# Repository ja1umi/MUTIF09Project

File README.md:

# MUTIF09 Project

MUTIF09 (or shortly MUTIF) project is my hobby project for developent of tiny homebrew computers and their add-on/expansion boards (e.g. Arithmetic coprocessor and I/O expansion board) simple enough for building and maintenance, focusing on around 1980s-era microprocessors (e.g. Motorola's MC6809, Harris' HD-6120) just for fun.

FAQ

1. When are updates available?

    Updates are available when they are released.

2. What does MUTIF mean?

    MUTIF is an anagram of two amaterur radio call signs of my own (suffix only).

3. How to assemble these things? / Where is the assembly manual?

    Refer to the schematic(s), order the PCB(s), collect parts required, populate the parts on the PCB just as you did in your other DIY electronics project. Knowledge of basic soldering techniques is also required. Remember to get your PC ready for USB-TTL serial cable installed.

    Like other open source projects, documents, sample programs and ohter design materials contained in this repository are provided *"as is"* without warranty.

    As for assembly manual(s), you can download the document(s) (e.g. *"Technical memorandum on MUTIF09 6809 Single Board Computer"* ) (for a fee) from BOOTH online store. Note: these booklet(s) are written in Japanese only.

    https://m-nihombashi.booth.pm/
    
    Or, you can get a copy at *doujinshi* sales exhibitions (e.g. Comic Maket, TechBookFest, Micom-Infinite PRO-68K).
    
    **I encourage you to get your copy of the booklet (if necessary) at the online store ( https://m-nihombashi.booth.pm/ ) due to the COVID-19 situation.**

4. Where is the document(s) about xxx?
    
    I know that documentation is insufficient, however, document preparation is still underway...

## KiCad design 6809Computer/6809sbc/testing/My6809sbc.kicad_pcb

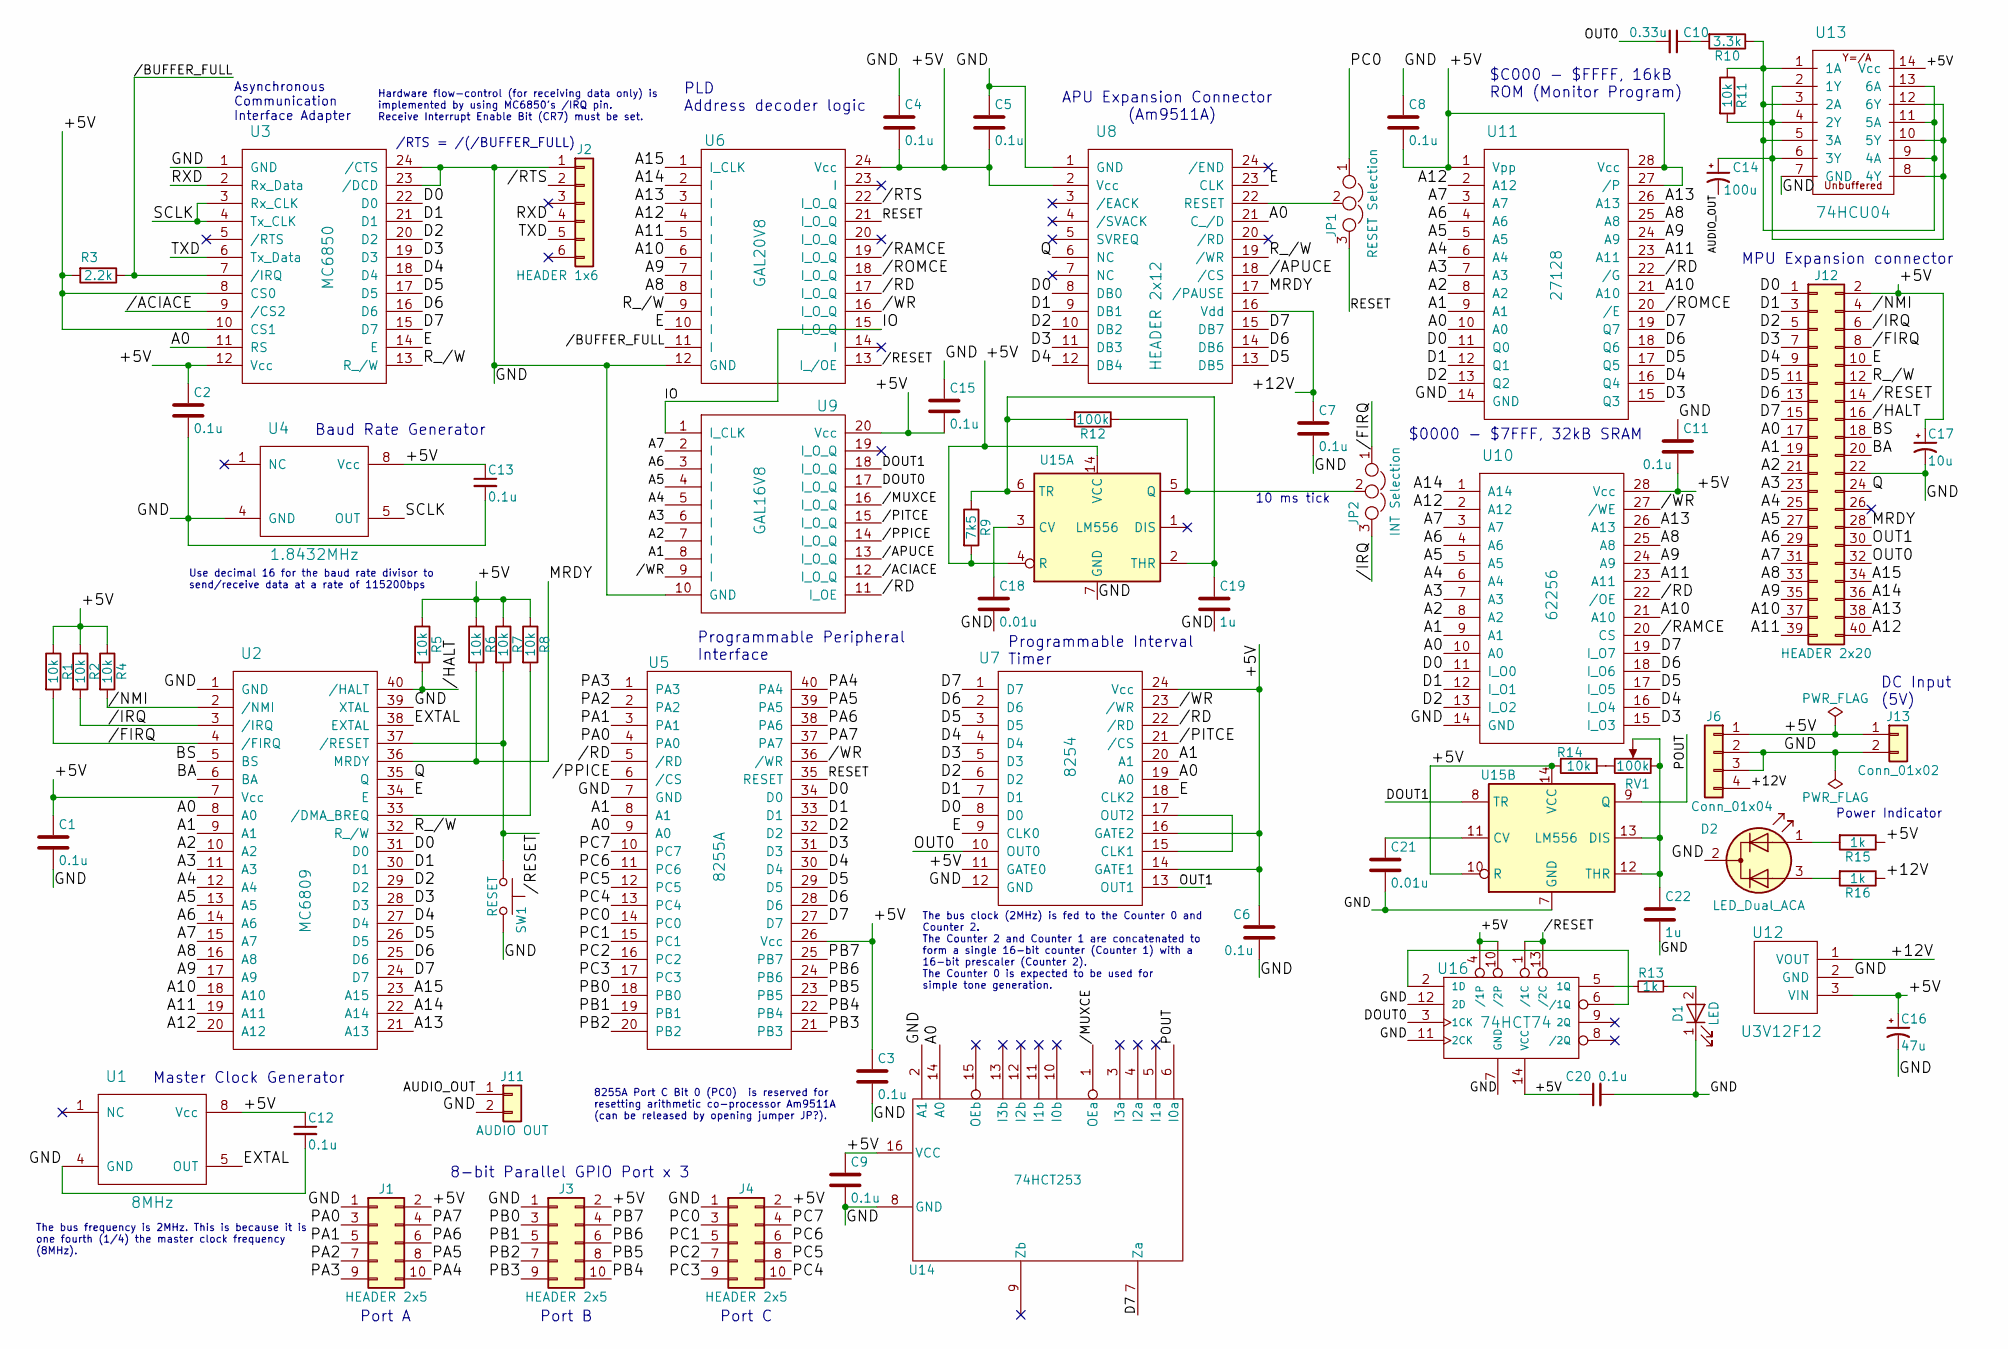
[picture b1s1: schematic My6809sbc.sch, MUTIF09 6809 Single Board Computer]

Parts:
C1, C2, C3, C4, C5, C6, C7, C8, C9, C11, C12, C13, C15, C20: 0.1u; C_Disc_D5.0mm_W2.5mm_P5.00mm
C10: 0.33u; C_Rect_L7.2mm_W3.5mm_P5.00mm_FKS2_FKP2_MKS2_MKP2
C14: 100u; CP_Radial_D8.0mm_P2.50mm
C16: 47u; CP_Radial_D5.0mm_P2.50mm
C17: 10u; CP_Radial_D5.0mm_P2.50mm
C18, C21: 0.01u; C_Disc_D5.0mm_W2.5mm_P5.00mm
C19, C22: 1u; C_Disc_D5.0mm_W2.5mm_P5.00mm
D1: LED; LED_D5.0mm
D2: LED_Dual_ACA; LED_D5.0mm-3
J1, J3, J4: HEADER 2x5; Pin_Header_Angled_2x05_Pitch2.54mm
J2: HEADER 1x6; Pin_Header_Angled_1x06_Pitch2.54mm
J6: Conn_01x04; Pin_Header_Straight_1x04_Pitch2.54mm
J11: AUDIO OUT; Pin_Header_Straight_1x02_Pitch2.54mm
J12: HEADER 2x20; Pin_Header_Straight_2x20_Pitch2.54mm
J13: Conn_01x02; Pin_Header_Straight_1x02_Pitch2.54mm
JP1: RESET Selection; Pin_Header_Straight_1x03_Pitch2.54mm
JP2: INT Selection; Pin_Header_Straight_1x03_Pitch2.54mm
R1, R2, R4, R5, R6, R7, R8, R11, R14: 10k; R_Axial_DIN0207_L6.3mm_D2.5mm_P10.16mm_Horizontal
R3: 2.2k; R_Axial_DIN0207_L6.3mm_D2.5mm_P10.16mm_Horizontal
R9: 7k5; R_Axial_DIN0207_L6.3mm_D2.5mm_P10.16mm_Horizontal
R10: 3.3k; R_Axial_DIN0207_L6.3mm_D2.5mm_P10.16mm_Horizontal
R12: 100k; R_Axial_DIN0207_L6.3mm_D2.5mm_P10.16mm_Horizontal
R13, R15, R16: 1k; R_Axial_DIN0207_L6.3mm_D2.5mm_P10.16mm_Horizontal
RV1: 100k; Potentiometer_WirePads_Small
SW1: RESET; SW_Tactile_Straight_KSA0Axx1LFTR
U1: 8MHz; Oscillator_DIP-8
U2: MC6809; DIP-40_W15.24mm_Socket
U3: MC6850; DIP-24_W15.24mm_Socket
U4: 1.8432MHz; Oscillator_DIP-8
U5: 8255A; DIP-40_W15.24mm_Socket
U6: GAL20V8; DIP-24_W7.62mm_Socket
U7: 8254; DIP-24_W15.24mm_Socket
U8: HEADER 2x12; DIP-24_W15.24mm_Socket
U9: GAL16V8; DIP-20_W7.62mm_Socket
U10: 62256; DIP-28_W15.24mm_Socket
U11: 27128; DIP-28_W15.24mm_Socket
U12: U3V12F12; Pin_Header_Straight_1x03_Pitch2.54mm
U13: 74HCU04; DIP-14_W7.62mm_Socket
U14: 74HCT253; DIP-16_W7.62mm_Socket
U15: LM556; DIP-14_W7.62mm_Socket
U16: 74HCT74; DIP-14_W7.62mm_Socket

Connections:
/+5V: C1.1, C2.1, C3.1, C4.2, C5.2, C6.1, C8.2, C9.1, C11.2, C12.1, C13.1, C15.2, C16.1, C17.1, C20.1, J1.2, J3.2, J4.2, J6.1, J12.2, J13.1, R1.1, R2.1, R3.2, R4.1, R5.1, R6.1, R7.1, R8.1, R9.2, R14.1, R15.1, U1.8 (Vcc), U2.7 (Vcc), U3.8 (CS0), U3.10 (CS1), U3.12 (Vcc), U4.8 (Vcc), U5.26 (Vcc), U6.24 (Vcc), U7.11 (GATE0), U7.14 (GATE1), U7.16 (GATE2), U7.24 (Vcc), U8.2 (Vcc), U9.20 (Vcc), U10.28 (Vcc), U11.1 (Vpp), U11.27 (/P), U11.28 (Vcc), U12.3 (VIN), U13.14 (Vcc), U14.16 (VCC), U15.4 (R), U15.10 (R), U15.14 (VCC), U16.4 (/1P), U16.10 (/2P), U16.14 (VCC)
/+12V: C7.1, J6.4, R16.1, U8.16 (Vdd), U12.1 (VOUT)
//ACIACE: U3.9 (/CS2), U9.12 (I_O_Q)
//APUCE: U8.18 (/CS), U9.13 (I_O_Q)
//BUFFER_FULL: R3.1, U3.7 (/IRQ), U6.11 (I)
//FIRQ: J12.8, JP2.1, R1.2, U2.4 (/FIRQ)
//HALT: J12.16, R5.2, U2.40 (/HALT)
//IRQ: J12.6, JP2.3, R2.2, U2.3 (/IRQ)
//MUXCE: U9.16 (I_O_Q), U14.1 (OEa)
//NMI: J12.4, R4.2, U2.2 (/NMI)
//PITCE: U7.21 (/CS), U9.15 (I_O_Q)
//PPICE: U5.6 (/CS), U9.14 (I_O_Q)
//RAMCE: U6.19 (I_O_Q), U10.20 (CS)
//RD: U5.5 (/RD), U6.17 (I_O_Q), U7.22 (/RD), U9.11 (I_OE), U10.22 (/OE), U11.22 (/G)
//RESET: J12.14, R7.2, SW1.1, U2.37 (/RESET), U6.13 (I_/OE), U16.1 (/1C), U16.13 (/2C)
//ROMCE: U6.18 (I_O_Q), U11.20 (/E)
//RTS: J2.2, U6.22 (I_O_Q)
//WR: U5.36 (/WR), U6.16 (I_O_Q), U7.23 (/WR), U9.9 (I), U10.27 (/WE)
/A0: J12.17, U2.8 (A0), U3.11 (RS), U5.9 (A0), U7.19 (A0), U8.21 (C_/D), U10.10 (A0), U11.10 (A0), U14.14 (A0)
/A1: J12.19, U2.9 (A1), U5.8 (A1), U7.20 (A1), U9.8 (I), U10.9 (A1), U11.9 (A1)
/A2: J12.21, U2.10 (A2), U9.7 (I), U10.8 (A2), U11.8 (A2)
/A3: J12.23, U2.11 (A3), U9.6 (I), U10.7 (A3), U11.7 (A3)
/A4: J12.25, U2.12 (A4), U9.5 (I), U10.6 (A4), U11.6 (A4)
/A5: J12.27, U2.13 (A5), U9.4 (I), U10.5 (A5), U11.5 (A5)
/A6: J12.29, U2.14 (A6), U9.3 (I), U10.4 (A6), U11.4 (A6)
/A7: J12.31, U2.15 (A7), U9.2 (I), U10.3 (A7), U11.3 (A7)
/A8: J12.33, U2.16 (A8), U6.8 (I), U10.25 (A8), U11.25 (A8)
/A9: J12.35, U2.17 (A9), U6.7 (I), U10.24 (A9), U11.24 (A9)
/A10: J12.37, U2.18 (A10), U6.6 (I), U10.21 (A10), U11.21 (A10)
/A11: J12.39, U2.19 (A11), U6.5 (I), U10.23 (A11), U11.23 (A11)
/A12: J12.40, U2.20 (A12), U6.4 (I), U10.2 (A12), U11.2 (A12)
/A13: J12.38, U2.21 (A13), U6.3 (I), U10.26 (A13), U11.26 (A13)
/A14: J12.36, U2.22 (A14), U6.2 (I), U10.1 (A14)
/A15: J12.34, U2.23 (A15), U6.1 (I_CLK)
/AUDIO_OUT: C14.2, J11.1
/BA: J12.20, U2.6 (BA)
/BS: J12.18, U2.5 (BS)
/D0: J12.1, U2.31 (D0), U3.22 (D0), U5.34 (D0), U7.8 (D0), U8.8 (DB0), U10.11 (I_O0), U11.11 (Q0)
/D1: J12.3, U2.30 (D1), U3.21 (D1), U5.33 (D1), U7.7 (D1), U8.9 (DB1), U10.12 (I_O1), U11.12 (Q1)
/D2: J12.5, U2.29 (D2), U3.20 (D2), U5.32 (D2), U7.6 (D2), U8.10 (DB2), U10.13 (I_O2), U11.13 (Q2)
/D3: J12.7, U2.28 (D3), U3.19 (D3), U5.31 (D3), U7.5 (D3), U8.11 (DB3), U10.15 (I_O3), U11.15 (Q3)
/D4: J12.9, U2.27 (D4), U3.18 (D4), U5.30 (D4), U7.4 (D4), U8.12 (DB4), U10.16 (I_O4), U11.16 (Q4)
/D5: J12.11, U2.26 (D5), U3.17 (D5), U5.29 (D5), U7.3 (D5), U8.13 (DB5), U10.17 (I_O5), U11.17 (Q5)
/D6: J12.13, U2.25 (D6), U3.16 (D6), U5.28 (D6), U7.2 (D6), U8.14 (DB6), U10.18 (I_O6), U11.18 (Q6)
/D7: J12.15, U2.24 (D7), U3.15 (D7), U5.27 (D7), U7.1 (D7), U8.15 (DB7), U10.19 (I_O7), U11.19 (Q7), U14.7 (Za)
/DOUT0: U9.17 (I_O_Q), U16.3 (1CK)
/DOUT1: U9.18 (I_O_Q), U15.8 (TR)
/E: J12.10, U2.34 (E), U3.14 (E), U6.10 (I), U7.9 (CLK0), U7.18 (CLK2), U8.23 (CLK)
/EXTAL: U1.5 (OUT), U2.38 (EXTAL)
/GND: C1.2, C2.2, C3.2, C4.1, C5.1, C6.2, C7.2, C8.1, C9.2, C11.1, C12.2, C13.2, C15.1, C16.2, C17.2, C18.2, C19.2, C20.2, C21.2, C22.2, D1.1 (K), D2.2 (K), J1.1, J2.1, J3.1, J4.1, J6.2, J6.3, J11.2, J12.22, J13.2, SW1.2, U1.4 (GND), U2.1 (GND), U2.39 (XTAL), U3.1 (GND), U3.23 (/DCD), U3.24 (/CTS), U4.4 (GND), U5.7 (GND), U6.12 (GND), U7.12 (GND), U8.1 (GND), U9.10 (GND), U10.14 (GND), U11.14 (GND), U12.2 (GND), U13.7 (GND), U14.2 (A1), U14.8 (GND), U15.7 (GND), U16.7 (GND), U16.11 (2CK), U16.12 (2D)
/IO: U6.15 (I_O_Q), U9.1 (I_CLK)
/MRDY: J12.28, R6.2, U2.36 (MRDY), U8.17 (/PAUSE)
/OUT0: C10.2, J12.32, U7.10 (OUT0)
/OUT1: J12.30, U7.13 (OUT1)
/PA0: J1.3, U5.4 (PA0)
/PA1: J1.5, U5.3 (PA1)
/PA2: J1.7, U5.2 (PA2)
/PA3: J1.9, U5.1 (PA3)
/PA4: J1.10, U5.40 (PA4)
/PA5: J1.8, U5.39 (PA5)
/PA6: J1.6, U5.38 (PA6)
/PA7: J1.4, U5.37 (PA7)
/PB0: J3.3, U5.18 (PB0)
/PB1: J3.5, U5.19 (PB1)
/PB2: J3.7, U5.20 (PB2)
/PB3: J3.9, U5.21 (PB3)
/PB4: J3.10, U5.22 (PB4)
/PB5: J3.8, U5.23 (PB5)
/PB6: J3.6, U5.24 (PB6)
/PB7: J3.4, U5.25 (PB7)
/PC0: J4.3, JP1.1, U5.14 (PC0)
/PC1: J4.5, U5.15 (PC1)
/PC2: J4.7, U5.16 (PC2)
/PC3: J4.9, U5.17 (PC3)
/PC4: J4.10, U5.13 (PC4)
/PC5: J4.8, U5.12 (PC5)
/PC6: J4.6, U5.11 (PC6)
/PC7: J4.4, U5.10 (PC7)
/POUT: U14.6 (I0a), U15.9 (Q)
/Q: J12.24, U2.35 (Q), U8.6 (NC)
/RESET: JP1.3, U5.35 (RESET), U6.21 (I_O_Q)
/RXD: J2.4, U3.2 (Rx_Data)
/R_/W: J12.12, U2.32 (R_/W), U3.13 (R_/W), U6.9 (I), U8.19 (/WR)
/SCLK: U3.3 (Rx_CLK), U3.4 (Tx_CLK), U4.5 (OUT)
/TXD: J2.5, U3.6 (Tx_Data)
unnamed: C10.1, R10.2
unnamed: C14.1, R11.2, U13.2 (1Y), U13.4 (2Y), U13.6 (3Y), U13.8 (4Y), U13.10 (5Y), U13.12 (6Y)
unnamed: C18.1, U15.3 (CV)
unnamed: C19.1, R9.1, R12.2, U15.2 (THR), U15.6 (TR)
unnamed: C21.1, U15.11 (CV)
unnamed: C22.1, RV1.1, RV1.2, U15.12 (THR), U15.13 (DIS)
unnamed: D1.2 (A), R13.1
unnamed: D2.1 (A1), R15.2
unnamed: D2.3 (A2), R16.2
unnamed: JP1.2, U8.22 (RESET)
unnamed: JP2.2, R12.1, U15.5 (Q)
unnamed: R8.2, U2.33 (/DMA_BREQ)
unnamed: R10.1, R11.1, U13.1 (1A), U13.3 (2A), U13.5 (3A), U13.9 (4A), U13.11 (5A), U13.13 (6A)
unnamed: R13.2, U16.5 (1Q)
unnamed: R14.2, RV1.3
unnamed: U7.15 (CLK1), U7.17 (OUT2)
unnamed: U16.2 (1D), U16.6 (/1Q)

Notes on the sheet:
MPU Expansion connector
DC Input (5V)
Baud Rate Generator
/RTS = /(/BUFFER_FULL)
Use decimal 16 for the baud rate divisor to send/receive data at a rate of 115200bps
8-bit Parallel GPIO Port x 3
Master Clock Generator
Programmable Interval Timer
Programmable Peripheral Interface
APU Expansion Connector (Am9511A)
PLD Address decoder logic
Asynchronous Communication Interface Adapter
$C000 - $FFFF, 16kB ROM (Monitor Program)
$0000 - $7FFF, 32kB SRAM
Hardware flow-control (for receiving data only) is implemented by using MC6850's /IRQ pin. Receive Interrupt Enable Bit (CR7) must be set.
The bus clock (2MHz) is fed to the Counter 0 and Counter 2. The Counter 2 and Counter 1 are concatenated to form a single 16-bit counter (Counter 1) with a 16-bit prescaler (Counter 2). The Counter 0 is expected to be used for simple tone generation.
The bus frequency is 2MHz. This is because it is one fourth (1/4) the master clock frequency (8MHz).
Port A
Port B
Port C
8255A Port C Bit 0 (PC0) is reserved for resetting arithmetic co-processor Am9511A (can be released by opening jumper JP?).
10 ms tick
Power Indicator

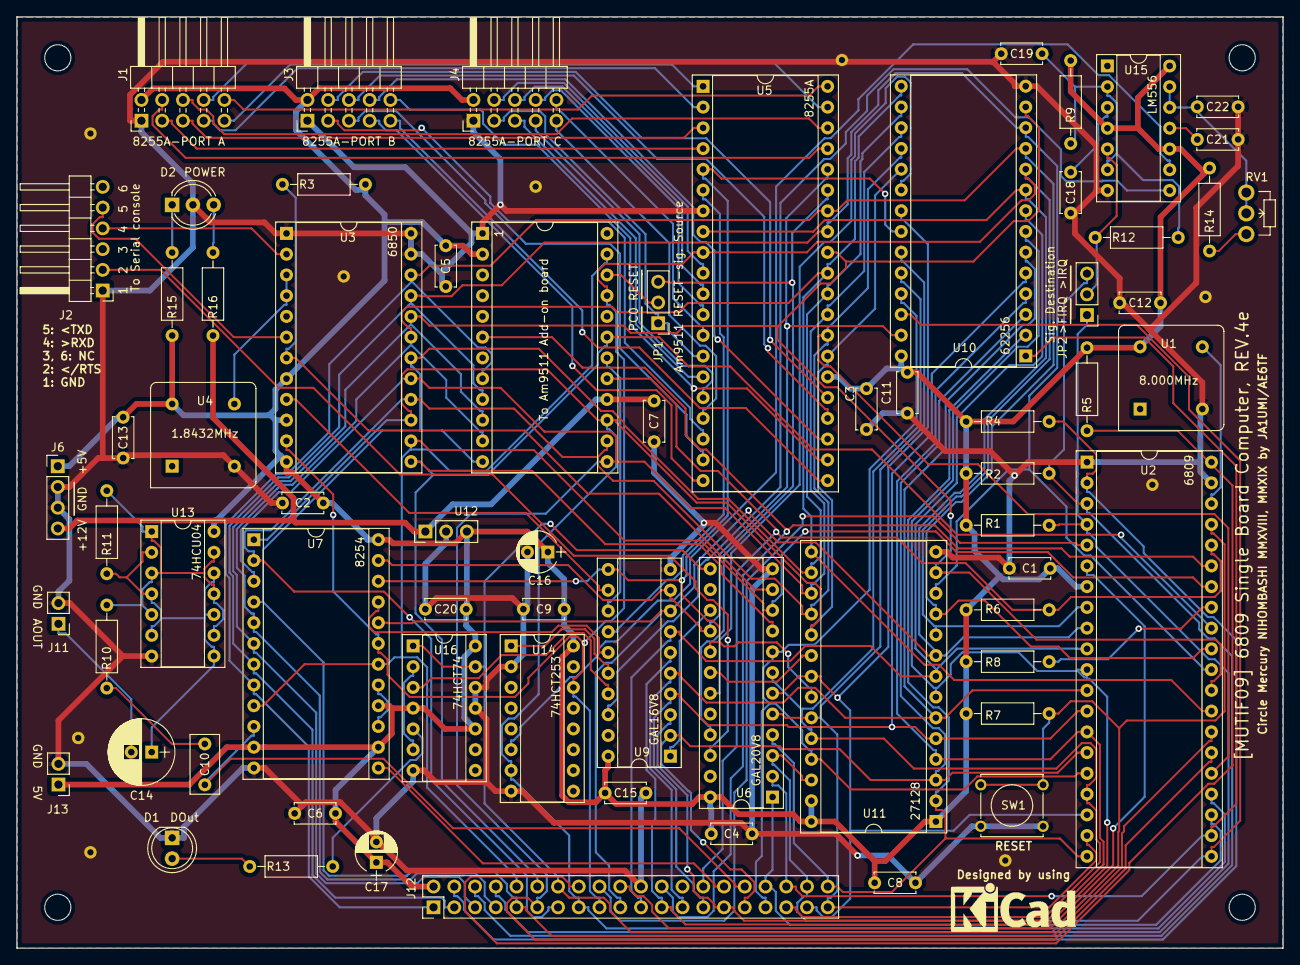
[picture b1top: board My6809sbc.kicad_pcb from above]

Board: 2 copper layers, 155.0 x 114.0 mm, 72 parts (0 on the bottom side), 102 nets.

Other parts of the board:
MH1, MH2, MH3, MH4: 3.2mm_M3; MountingHole_3.2mm_M3

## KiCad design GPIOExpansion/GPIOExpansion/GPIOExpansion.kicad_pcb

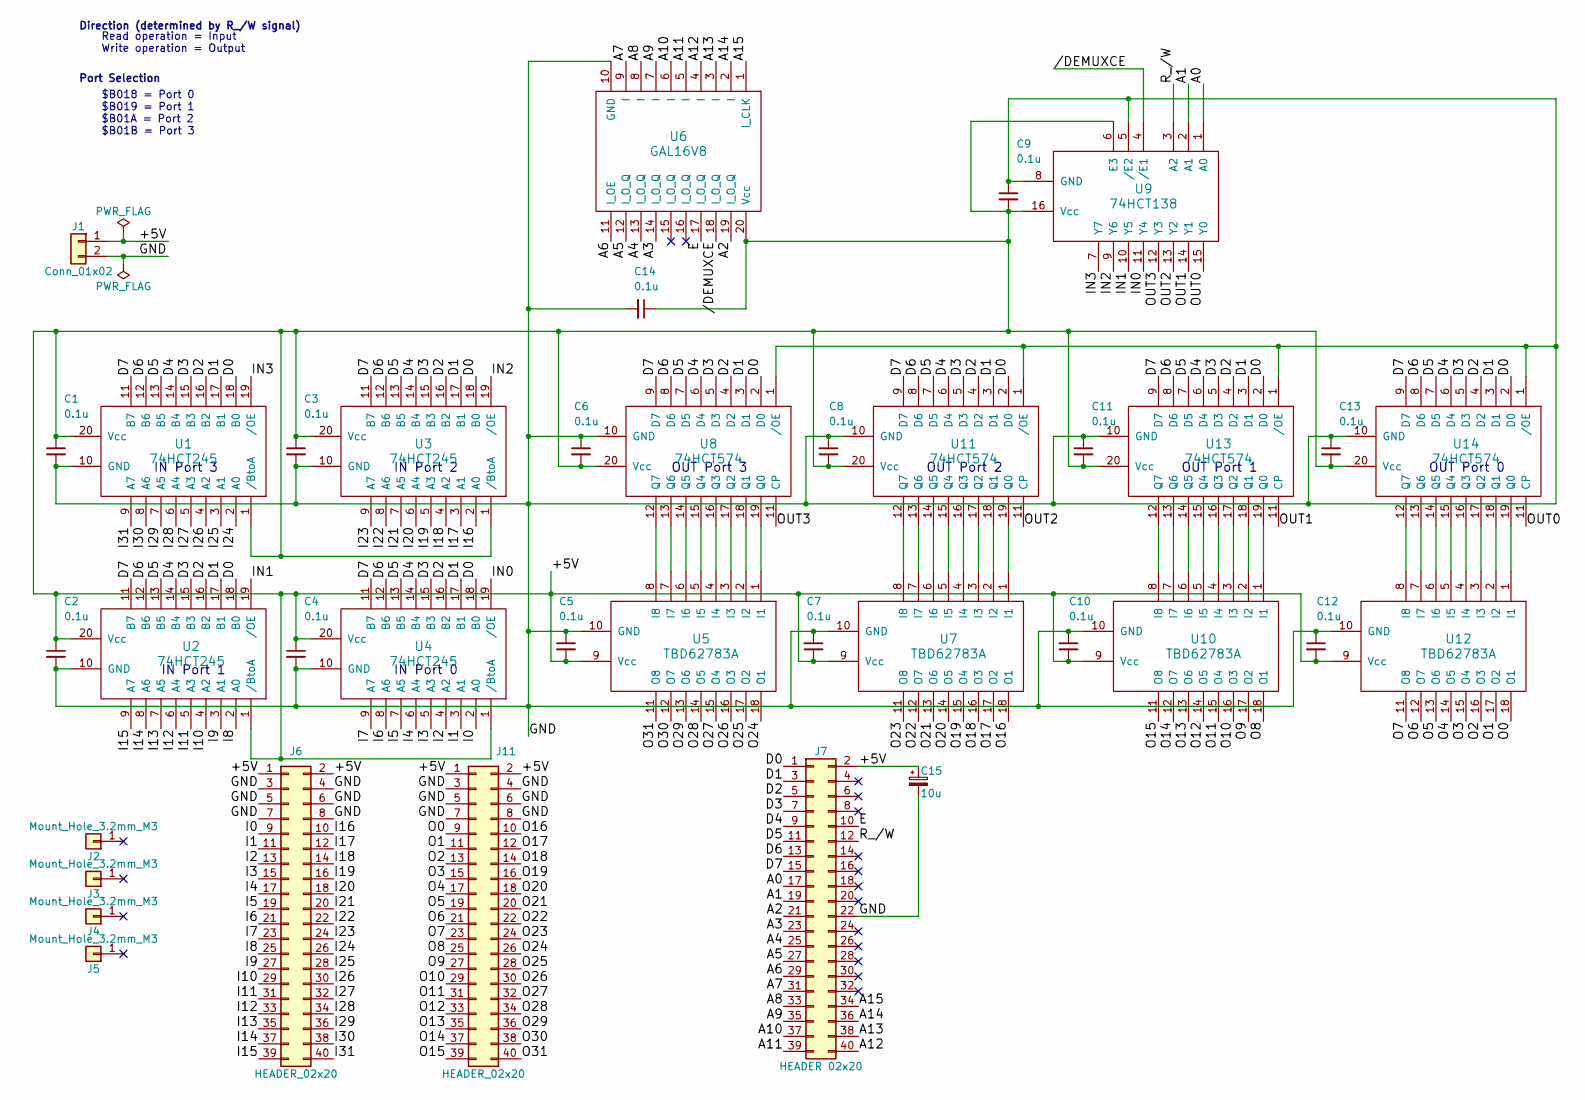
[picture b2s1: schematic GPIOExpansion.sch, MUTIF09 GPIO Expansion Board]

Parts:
C1, C2, C3, C4, C5, C6, C7, C8, C9, C10, C11, C12, C13, C14: 0.1u; C_Disc_D5.0mm_W2.5mm_P5.00mm
C15: 10u; CP_Radial_D5.0mm_P2.50mm
J1: Conn_01x02; Pin_Header_Straight_1x02_Pitch2.54mm
J2, J3, J4, J5: Mount_Hole_3.2mm_M3; MountingHole_3.2mm_M3
J6, J11: HEADER_02x20; Pin_Header_Angled_2x20_Pitch2.54mm
J7: HEADER 02x20; Pin_Header_Straight_2x20_Pitch2.54mm
U1, U2, U3, U4: 74HCT245; DIP-20_W7.62mm
U5, U7, U10, U12: TBD62783A; DIP-18_W7.62mm
U6: GAL16V8; DIP-20_W7.62mm_Socket
U8, U11, U13, U14: 74HCT574; DIP-20_W7.62mm_Socket
U9: 74HCT138; DIP-16_W7.62mm

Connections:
/+5V: C1.1, C2.1, C3.1, C4.1, C5.2, C6.2, C7.2, C8.2, C9.2, C10.2, C11.2, C12.2, C13.2, C14.1, C15.1, J1.1, J6.1, J6.2, J7.2, J11.1, J11.2, U1.1 (/BtoA), U1.20 (Vcc), U2.1 (/BtoA), U2.20 (Vcc), U3.1 (/BtoA), U3.20 (Vcc), U4.1 (/BtoA), U4.20 (Vcc), U5.9 (Vcc), U6.20 (Vcc), U7.9 (Vcc), U8.20 (Vcc), U9.6 (E3), U9.16 (Vcc), U10.9 (Vcc), U11.20 (Vcc), U12.9 (Vcc), U13.20 (Vcc), U14.20 (Vcc)
//DEMUXCE: U6.18 (I_O_Q), U9.4 (/E1)
/A0: J7.17, U9.1 (A0)
/A1: J7.19, U9.2 (A1)
/A2: J7.21, U6.19 (I_O_Q)
/A3: J7.23, U6.14 (I_O_Q)
/A4: J7.25, U6.13 (I_O_Q)
/A5: J7.27, U6.12 (I_O_Q)
/A6: J7.29, U6.11 (I_OE)
/A7: J7.31, U6.9 (I)
/A8: J7.33, U6.8 (I)
/A9: J7.35, U6.7 (I)
/A10: J7.37, U6.6 (I)
/A11: J7.39, U6.5 (I)
/A12: J7.40, U6.4 (I)
/A13: J7.38, U6.3 (I)
/A14: J7.36, U6.2 (I)
/A15: J7.34, U6.1 (I_CLK)
/D0: J7.1, U1.18 (B0), U2.18 (B0), U3.18 (B0), U4.18 (B0), U8.2 (D0), U11.2 (D0), U13.2 (D0), U14.2 (D0)
/D1: J7.3, U1.17 (B1), U2.17 (B1), U3.17 (B1), U4.17 (B1), U8.3 (D1), U11.3 (D1), U13.3 (D1), U14.3 (D1)
/D2: J7.5, U1.16 (B2), U2.16 (B2), U3.16 (B2), U4.16 (B2), U8.4 (D2), U11.4 (D2), U13.4 (D2), U14.4 (D2)
/D3: J7.7, U1.15 (B3), U2.15 (B3), U3.15 (B3), U4.15 (B3), U8.5 (D3), U11.5 (D3), U13.5 (D3), U14.5 (D3)
/D4: J7.9, U1.14 (B4), U2.14 (B4), U3.14 (B4), U4.14 (B4), U8.6 (D4), U11.6 (D4), U13.6 (D4), U14.6 (D4)
/D5: J7.11, U1.13 (B5), U2.13 (B5), U3.13 (B5), U4.13 (B5), U8.7 (D5), U11.7 (D5), U13.7 (D5), U14.7 (D5)
/D6: J7.13, U1.12 (B6), U2.12 (B6), U3.12 (B6), U4.12 (B6), U8.8 (D6), U11.8 (D6), U13.8 (D6), U14.8 (D6)
/D7: J7.15, U1.11 (B7), U2.11 (B7), U3.11 (B7), U4.11 (B7), U8.9 (D7), U11.9 (D7), U13.9 (D7), U14.9 (D7)
/GND: C1.2, C2.2, C3.2, C4.2, C5.1, C6.1, C7.1, C8.1, C9.1, C10.1, C11.1, C12.1, C13.1, C14.2, C15.2, J1.2, J6.3, J6.4, J6.5, J6.6, J6.7, J6.8, J7.22, J11.3, J11.4, J11.5, J11.6, J11.7, J11.8, U1.10 (GND), U2.10 (GND), U3.10 (GND), U4.10 (GND), U5.10 (GND), U6.10 (GND), U7.10 (GND), U8.1 (/OE), U8.10 (GND), U9.5 (/E2), U9.8 (GND), U10.10 (GND), U11.1 (/OE), U11.10 (GND), U12.10 (GND), U13.1 (/OE), U13.10 (GND), U14.1 (/OE), U14.10 (GND)
/I0: J6.9, U4.2 (A0)
/I1: J6.11, U4.3 (A1)
/I2: J6.13, U4.4 (A2)
/I3: J6.15, U4.5 (A3)
/I4: J6.17, U4.6 (A4)
/I5: J6.19, U4.7 (A5)
/I6: J6.21, U4.8 (A6)
/I7: J6.23, U4.9 (A7)
/I8: J6.25, U2.2 (A0)
/I9: J6.27, U2.3 (A1)
/I10: J6.29, U2.4 (A2)
/I11: J6.31, U2.5 (A3)
/I12: J6.33, U2.6 (A4)
/I13: J6.35, U2.7 (A5)
/I14: J6.37, U2.8 (A6)
/I15: J6.39, U2.9 (A7)
/I16: J6.10, U3.2 (A0)
/I17: J6.12, U3.3 (A1)
/I18: J6.14, U3.4 (A2)
/I19: J6.16, U3.5 (A3)
/I20: J6.18, U3.6 (A4)
/I21: J6.20, U3.7 (A5)
/I22: J6.22, U3.8 (A6)
/I23: J6.24, U3.9 (A7)
/I24: J6.26, U1.2 (A0)
/I25: J6.28, U1.3 (A1)
/I26: J6.30, U1.4 (A2)
/I27: J6.32, U1.5 (A3)
/I28: J6.34, U1.6 (A4)
/I29: J6.36, U1.7 (A5)
/I30: J6.38, U1.8 (A6)
/I31: J6.40, U1.9 (A7)
/IN0: U4.19 (/OE), U9.11 (Y4)
/IN1: U2.19 (/OE), U9.10 (Y5)
/IN2: U3.19 (/OE), U9.9 (Y6)
/IN3: U1.19 (/OE), U9.7 (Y7)
/O0: J11.9, U12.18 (O1)
/O1: J11.11, U12.17 (O2)
/O2: J11.13, U12.16 (O3)
/O3: J11.15, U12.15 (O4)
/O4: J11.17, U12.14 (O5)
/O5: J11.19, U12.13 (O6)
/O6: J11.21, U12.12 (O7)
/O7: J11.23, U12.11 (O8)
/O8: J11.25, U10.18 (O1)
/O9: J11.27, U10.17 (O2)
/O10: J11.29, U10.16 (O3)
/O11: J11.31, U10.15 (O4)
/O12: J11.33, U10.14 (O5)
/O13: J11.35, U10.13 (O6)
/O14: J11.37, U10.12 (O7)
/O15: J11.39, U10.11 (O8)
/O16: J11.10, U7.18 (O1)
/O17: J11.12, U7.17 (O2)
/O18: J11.14, U7.16 (O3)
/O19: J11.16, U7.15 (O4)
/O20: J11.18, U7.14 (O5)
/O21: J11.20, U7.13 (O6)
/O22: J11.22, U7.12 (O7)
/O23: J11.24, U7.11 (O8)
/O24: J11.26, U5.18 (O1)
/O25: J11.28, U5.17 (O2)
/O26: J11.30, U5.16 (O3)
/O27: J11.32, U5.15 (O4)
/O28: J11.34, U5.14 (O5)
/O29: J11.36, U5.13 (O6)
/O30: J11.38, U5.12 (O7)
/O31: J11.40, U5.11 (O8)
/OUT0: U9.15 (Y0), U14.11 (CP)
/OUT1: U9.14 (Y1), U13.11 (CP)
/OUT2: U9.13 (Y2), U11.11 (CP)
/OUT3: U8.11 (CP), U9.12 (Y3)
/R_/W: J7.12, U9.3 (A2)
unnamed: U5.1 (I1), U8.19 (Q0)
unnamed: U5.2 (I2), U8.18 (Q1)
unnamed: U5.3 (I3), U8.17 (Q2)
unnamed: U5.4 (I4), U8.16 (Q3)
unnamed: U5.5 (I5), U8.15 (Q4)
unnamed: U5.6 (I6), U8.14 (Q5)
unnamed: U5.7 (I7), U8.13 (Q6)
unnamed: U5.8 (I8), U8.12 (Q7)
unnamed: U10.1 (I1), U13.19 (Q0)
unnamed: U10.2 (I2), U13.18 (Q1)
unnamed: U10.3 (I3), U13.17 (Q2)
unnamed: U10.4 (I4), U13.16 (Q3)
unnamed: U10.5 (I5), U13.15 (Q4)
unnamed: U10.6 (I6), U13.14 (Q5)
unnamed: U10.7 (I7), U13.13 (Q6)
unnamed: U10.8 (I8), U13.12 (Q7)
unnamed: U7.8 (I8), U11.12 (Q7)
unnamed: U7.7 (I7), U11.13 (Q6)
unnamed: U7.6 (I6), U11.14 (Q5)
unnamed: U7.5 (I5), U11.15 (Q4)
unnamed: U7.4 (I4), U11.16 (Q3)
unnamed: U7.3 (I3), U11.17 (Q2)
unnamed: U7.2 (I2), U11.18 (Q1)
unnamed: U7.1 (I1), U11.19 (Q0)
unnamed: U12.1 (I1), U14.19 (Q0)
unnamed: U12.2 (I2), U14.18 (Q1)
unnamed: U12.3 (I3), U14.17 (Q2)
unnamed: U12.4 (I4), U14.16 (Q3)
unnamed: U12.5 (I5), U14.15 (Q4)
unnamed: U12.6 (I6), U14.14 (Q5)
unnamed: U12.7 (I7), U14.13 (Q6)
unnamed: U12.8 (I8), U14.12 (Q7)

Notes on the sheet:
Port Selection
$B018 = Port 0 $B019 = Port 1 $B01A = Port 2 $B01B = Port 3
Direction (determined by R_/W signal)
Read operation = Input Write operation = Output
IN Port 3
IN Port 2
IN Port 1
IN Port 0
OUT Port 3
OUT Port 2
OUT Port 1
OUT Port 0

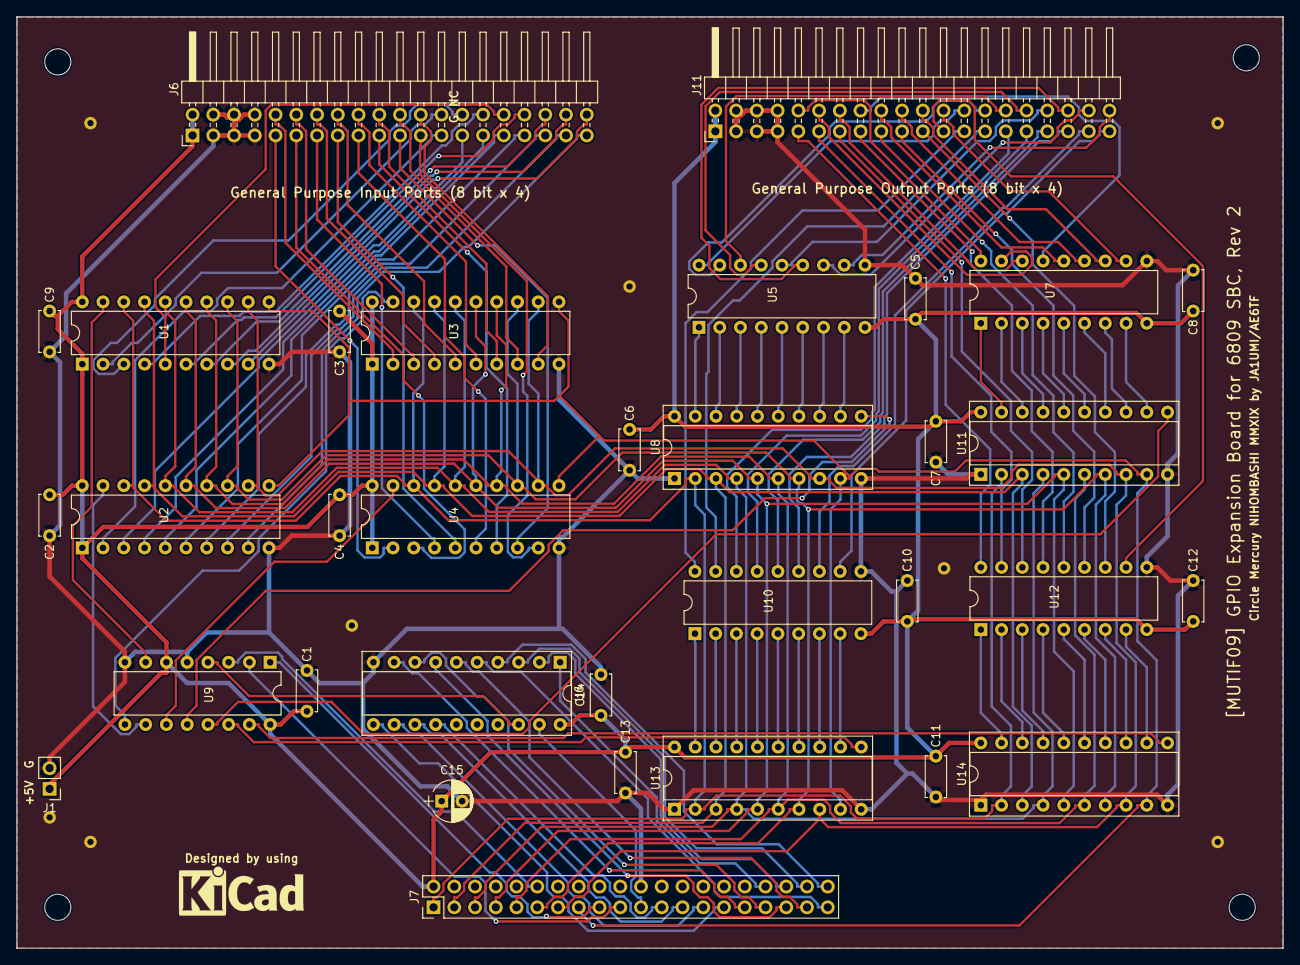
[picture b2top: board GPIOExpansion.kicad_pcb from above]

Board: 2 copper layers, 155.0 x 114.0 mm, 37 parts (0 on the bottom side), 132 nets.

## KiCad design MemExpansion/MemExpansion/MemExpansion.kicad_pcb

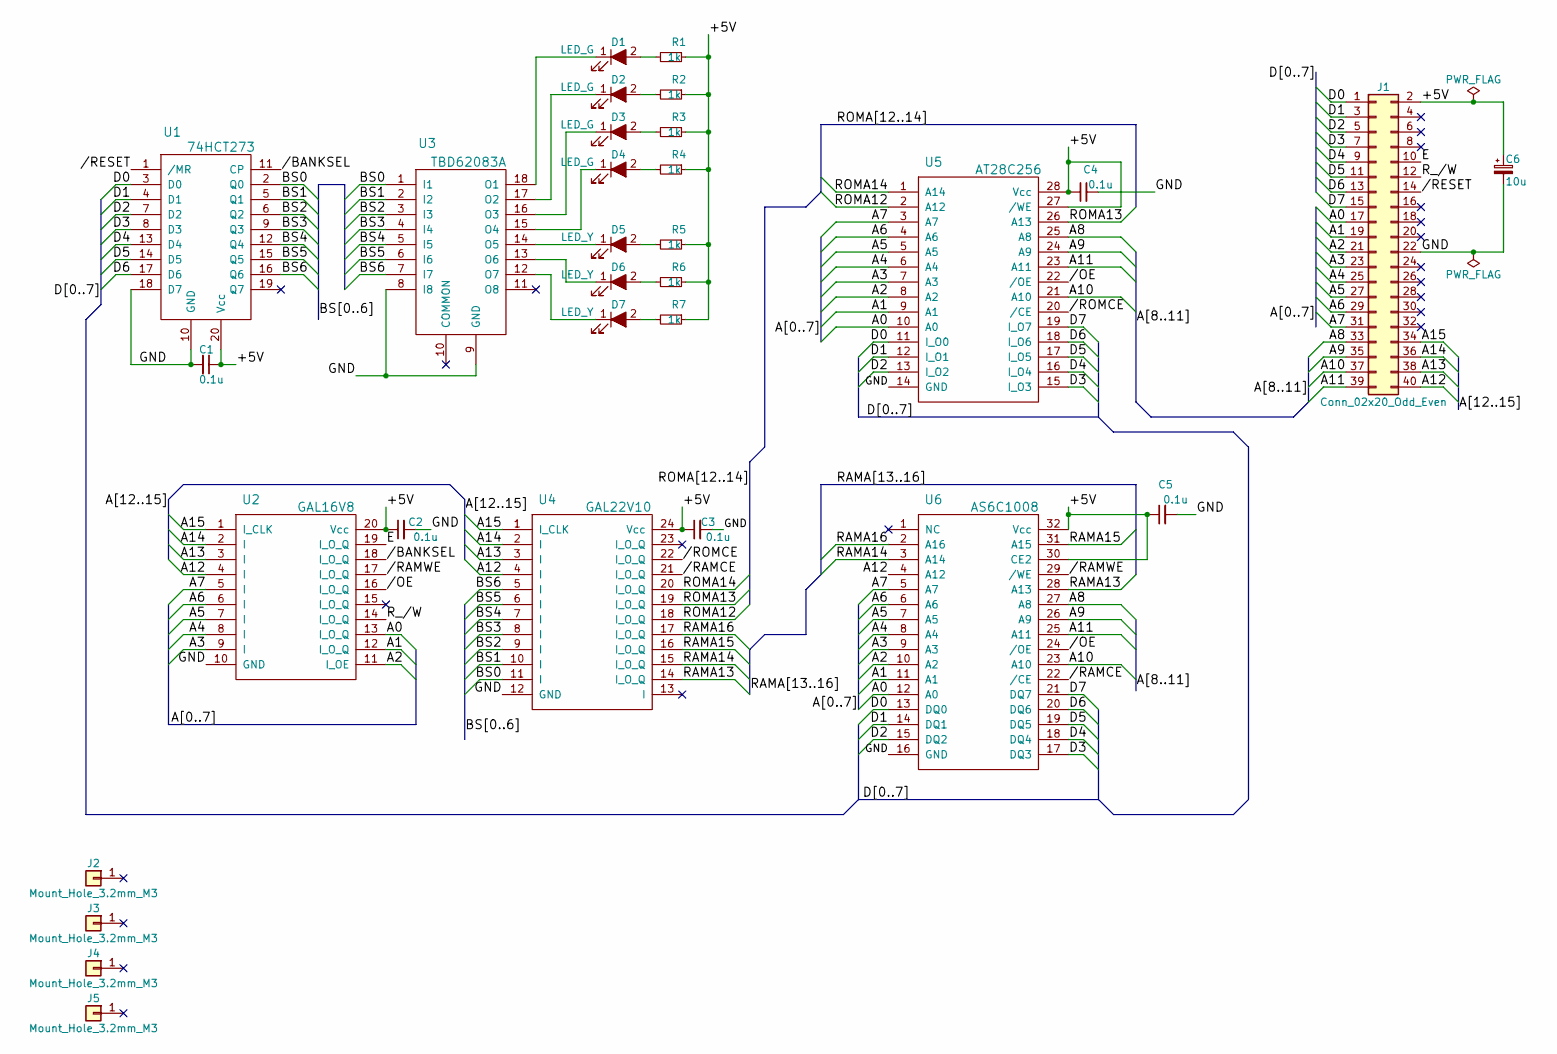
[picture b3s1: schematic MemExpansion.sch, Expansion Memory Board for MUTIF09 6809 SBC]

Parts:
C1, C2, C3, C4, C5: 0.1u; C_Disc_D5.0mm_W2.5mm_P5.00mm
C6: 10u; CP_Radial_D5.0mm_P2.50mm
D1, D2, D3, D4: LED_G; LED_D5.0mm
D5, D6, D7: LED_Y; LED_D5.0mm
J1: Conn_02x20_Odd_Even; Pin_Header_Straight_2x20_Pitch2.54mm
J2, J3, J4, J5: Mount_Hole_3.2mm_M3; MountingHole_3.2mm_M3
R1, R2, R3, R4, R5, R6, R7: 1k; R_Axial_DIN0207_L6.3mm_D2.5mm_P10.16mm_Horizontal
U1: 74HCT273; DIP-20_W7.62mm
U2: GAL16V8; DIP-20_W7.62mm
U3: TBD62083A; DIP-18_W7.62mm
U4: GAL22V10; DIP-24_W7.62mm
U5: AT28C256; DIP-28_W15.24mm
U6: AS6C1008; DIP-32_W15.24mm

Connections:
/+5V: C1.1, C2.1, C3.1, C4.1, C5.1, C6.1, J1.2, R1.1, R2.1, R3.1, R4.1, R5.1, R6.1, R7.1, U1.20 (Vcc), U2.20 (Vcc), U4.24 (Vcc), U5.27 (/WE), U5.28 (Vcc), U6.30 (CE2), U6.32 (Vcc)
//BANKSEL: U1.11 (CP), U2.18 (I_O_Q)
//OE: U2.16 (I_O_Q), U5.22 (/OE), U6.24 (/OE)
//RAMCE: U4.21 (I_O_Q), U6.22 (/CE)
//RAMWE: U2.17 (I_O_Q), U6.29 (/WE)
//RESET: J1.14, U1.1 (/MR)
//ROMCE: U4.22 (I_O_Q), U5.20 (/CE)
/A0: J1.17, U2.13 (I_O_Q), U5.10 (A0), U6.12 (A0)
/A1: J1.19, U2.12 (I_O_Q), U5.9 (A1), U6.11 (A1)
/A2: J1.21, U2.11 (I_OE), U5.8 (A2), U6.10 (A2)
/A3: J1.23, U2.9 (I), U5.7 (A3), U6.9 (A3)
/A4: J1.25, U2.8 (I), U5.6 (A4), U6.8 (A4)
/A5: J1.27, U2.7 (I), U5.5 (A5), U6.7 (A5)
/A6: J1.29, U2.6 (I), U5.4 (A6), U6.6 (A6)
/A7: J1.31, U2.5 (I), U5.3 (A7), U6.5 (A7)
/A8: J1.33, U5.25 (A8), U6.27 (A8)
/A9: J1.35, U5.24 (A9), U6.26 (A9)
/A10: J1.37, U5.21 (A10), U6.23 (A10)
/A11: J1.39, U5.23 (A11), U6.25 (A11)
/A12: J1.40, U2.4 (I), U4.4 (I), U6.4 (A12)
/A13: J1.38, U2.3 (I), U4.3 (I)
/A14: J1.36, U2.2 (I), U4.2 (I)
/A15: J1.34, U2.1 (I_CLK), U4.1 (I_CLK)
/BS0: U1.2 (Q0), U3.1 (I1), U4.11 (I)
/BS1: U1.5 (Q1), U3.2 (I2), U4.10 (I)
/BS2: U1.6 (Q2), U3.3 (I3), U4.9 (I)
/BS3: U1.9 (Q3), U3.4 (I4), U4.8 (I)
/BS4: U1.12 (Q4), U3.5 (I5), U4.7 (I)
/BS5: U1.15 (Q5), U3.6 (I6), U4.6 (I)
/BS6: U1.16 (Q6), U3.7 (I7), U4.5 (I)
/D0: J1.1, U1.3 (D0), U5.11 (I_O0), U6.13 (DQ0)
/D1: J1.3, U1.4 (D1), U5.12 (I_O1), U6.14 (DQ1)
/D2: J1.5, U1.7 (D2), U5.13 (I_O2), U6.15 (DQ2)
/D3: J1.7, U1.8 (D3), U5.15 (I_O3), U6.17 (DQ3)
/D4: J1.9, U1.13 (D4), U5.16 (I_O4), U6.18 (DQ4)
/D5: J1.11, U1.14 (D5), U5.17 (I_O5), U6.19 (DQ5)
/D6: J1.13, U1.17 (D6), U5.18 (I_O6), U6.20 (DQ6)
/D7: J1.15, U5.19 (I_O7), U6.21 (DQ7)
/E: J1.10, U2.19 (I_O_Q)
/GND: C1.2, C2.2, C3.2, C4.2, C5.2, C6.2, J1.22, U1.10 (GND), U1.18 (D7), U2.10 (GND), U3.8 (I8), U3.9 (GND), U4.12 (GND), U5.14 (GND), U6.16 (GND)
/RAMA13: U4.14 (I_O_Q), U6.28 (A13)
/RAMA14: U4.15 (I_O_Q), U6.3 (A14)
/RAMA15: U4.16 (I_O_Q), U6.31 (A15)
/RAMA16: U4.17 (I_O_Q), U6.2 (A16)
/ROMA12: U4.18 (I_O_Q), U5.2 (A12)
/ROMA13: U4.19 (I_O_Q), U5.26 (A13)
/ROMA14: U4.20 (I_O_Q), U5.1 (A14)
/R_/W: J1.12, U2.14 (I_O_Q)
unnamed: D1.1 (K), U3.18 (O1)
unnamed: D1.2 (A), R1.2
unnamed: D2.1 (K), U3.17 (O2)
unnamed: D2.2 (A), R2.2
unnamed: D3.1 (K), U3.16 (O3)
unnamed: D3.2 (A), R3.2
unnamed: D4.1 (K), U3.15 (O4)
unnamed: D4.2 (A), R4.2
unnamed: D5.1 (K), U3.14 (O5)
unnamed: D5.2 (A), R5.2
unnamed: D6.1 (K), U3.13 (O6)
unnamed: D6.2 (A), R6.2
unnamed: D7.1 (K), U3.12 (O7)
unnamed: D7.2 (A), R7.2

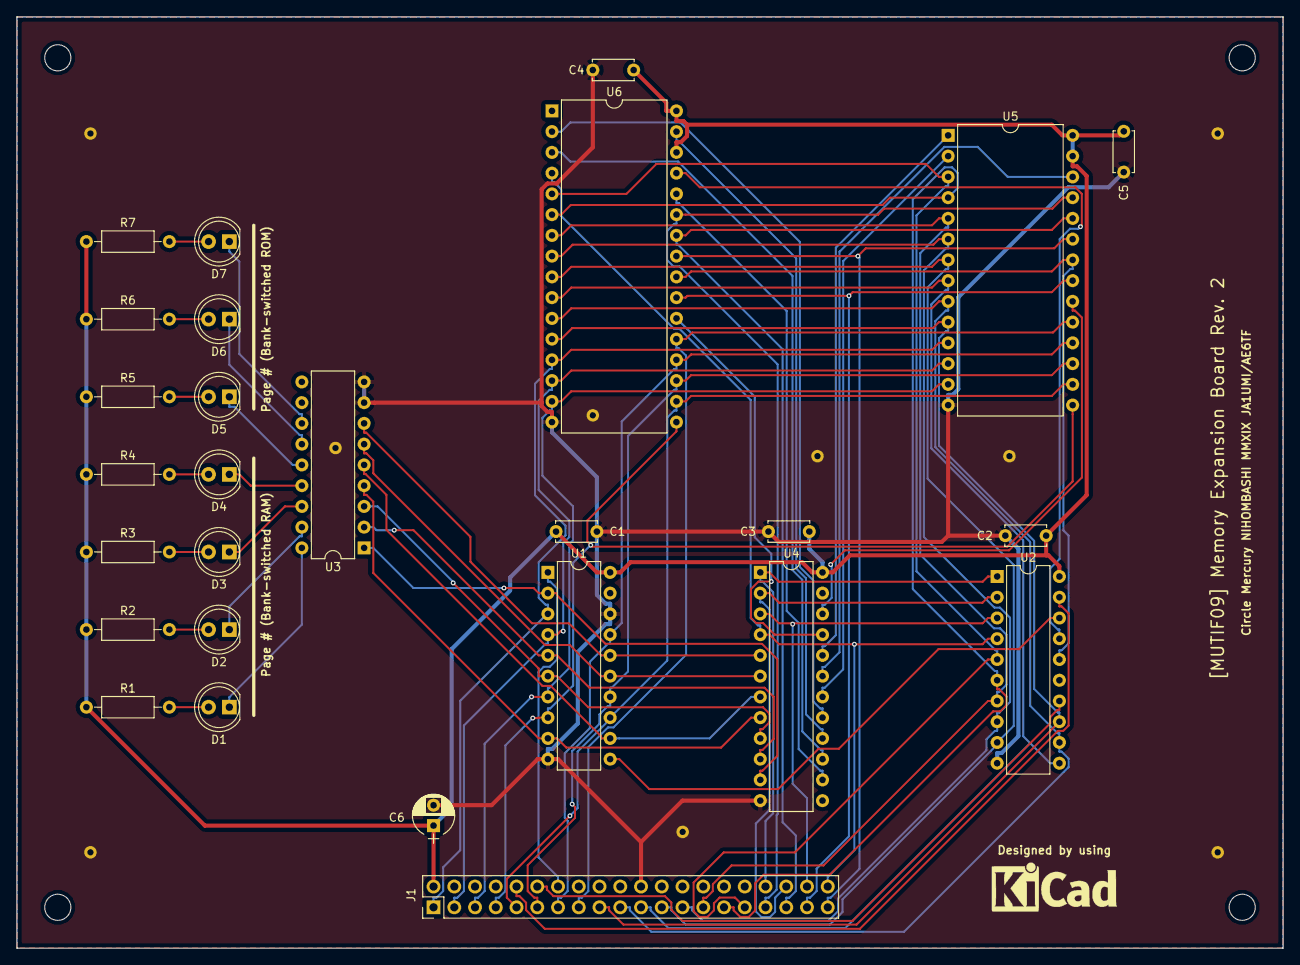
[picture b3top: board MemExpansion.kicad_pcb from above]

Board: 2 copper layers, 155.0 x 114.0 mm, 31 parts (0 on the bottom side), 62 nets.
